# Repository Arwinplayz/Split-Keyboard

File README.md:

# Split-Keyboard
A custom **split keyboard** project built with kicad, fusion 360 and kmk.
---

## Project Overview

This keyboard is a **split design**, fully programmable using KMK firmware. The goal was to design something that would provide a decent typing experience and replace my current keyboard.
---

## Screenshots

### 1. Overall

### 2. Schematic

### 3. PCB layout

### 4. Case Assembly

### Bill Of Materials

| Item | Description | Qty | Unit Price (AUD) | Total Price (AUD) | URL | Running Total (AUD) | USD |
|------|------------|-----|------------------|-------------------|-----|---------------------|-----|
| Kailh Choc Hotswap Socket x10 | Hotswap socket | 1 | $1.52 | $1.52 | [AliExpress](https://www.aliexpress.com/item/1005009439757444.html) | $1.52 | $1.00 |
| Rotary Encoder Module EC11 | Rotary encoder with knob | 2 | $0.43 | $0.86 | [Alibaba](https://www.alibaba.com/product-detail/Yuwah-Factory-Sale-Linear-rotary-Encoder_1601398686693.html) | $2.38 | $1.57 |
| Rotary Encoder Control Button Knob | Rotary encoder knob | 2 | $3.14 | $6.28 | [AliExpress](https://www.aliexpress.com/item/1005002930536102.html) | $8.66 | $5.71 |
| Kailh Low Profile Choc Brown (30 pack) | Switches | 2 | $27.99 | $55.98 | [AliExpress](https://www.aliexpress.com/item/1005005970877769.html) | $58.36 | $38.51 |
| Kailh CHOC Slim Keycaps – Milky White (10 pack) | Keycaps | 2 | $15.69 | $31.38 | [AliExpress](https://www.aliexpress.com/item/1005009153609513.html) | $89.74 | $59.21 |
| 402050 LiPo Battery | Battery | 2 | $3.80 | $7.60 | [AliExpress](https://www.aliexpress.com/item/32662701530.html) | $97.34 | $64.23 |
| JLCPCB Manufacturing | PCB | 1 | $33.00 | $33.00 | [JLCPCB](https://cart.jlcpcb.com/quote) | $130.34 | $86.04 |
| 3D Printed Case | Case | 1 | – | – | – | $130.34 | $86.04 |

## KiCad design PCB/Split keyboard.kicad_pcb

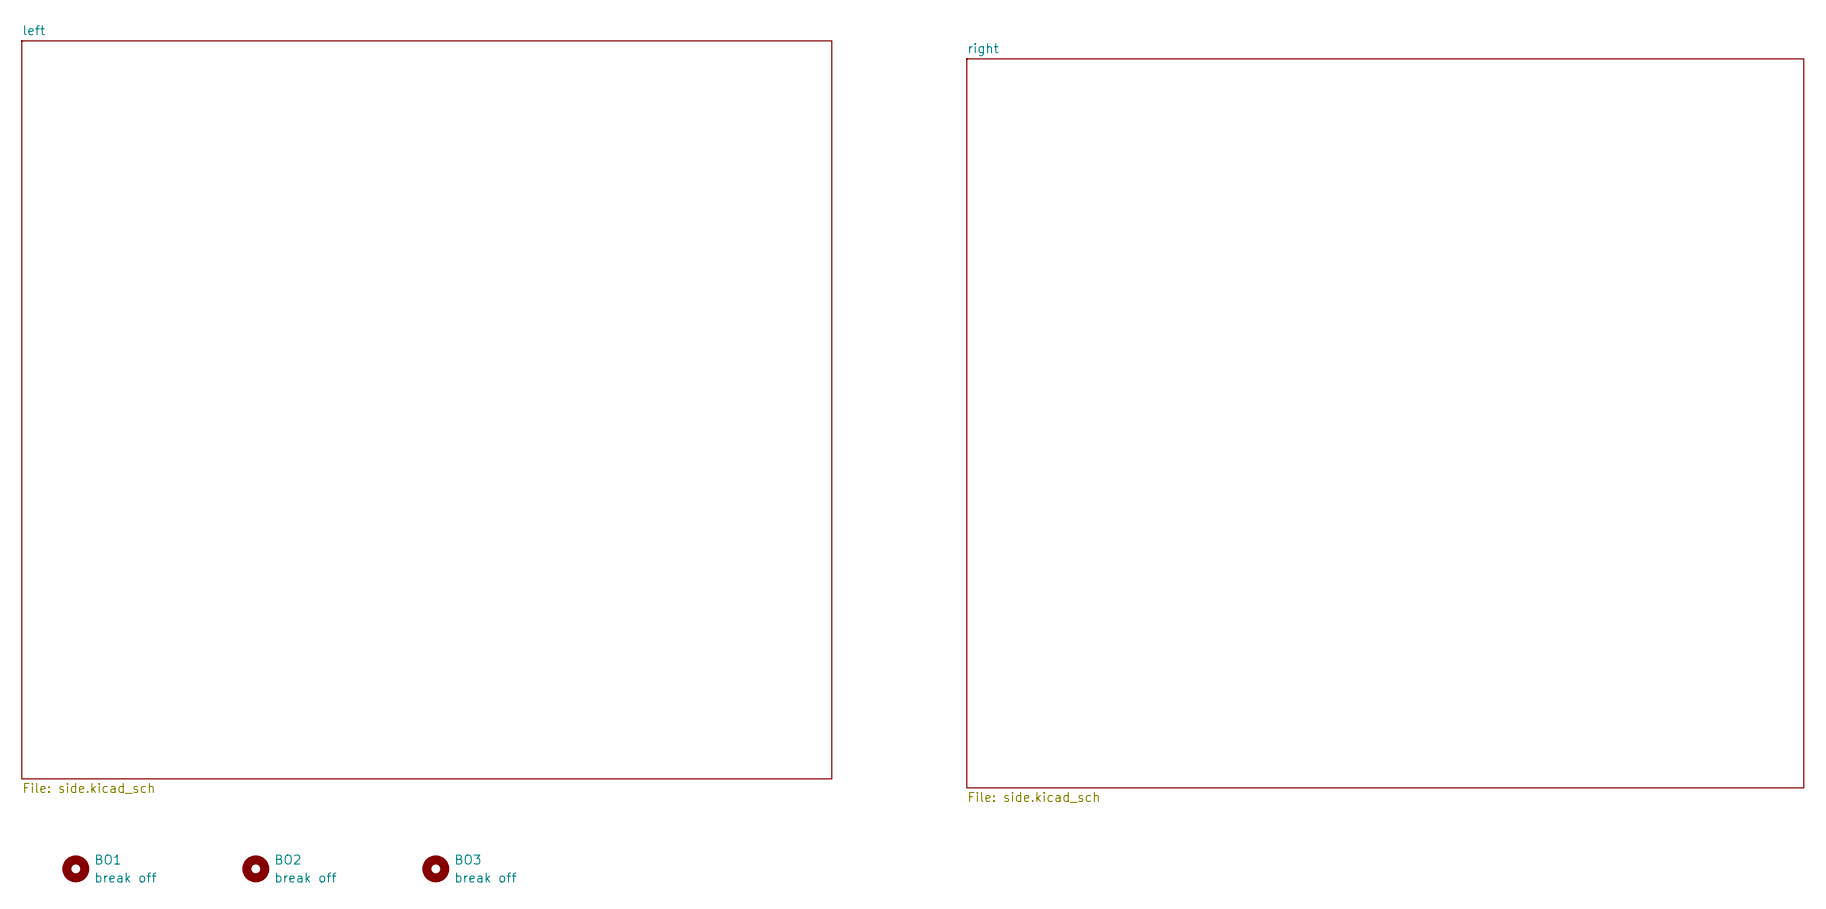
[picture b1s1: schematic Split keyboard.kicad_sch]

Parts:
BO1, BO2, BO3: break off; mouse-bite-5mm-slot

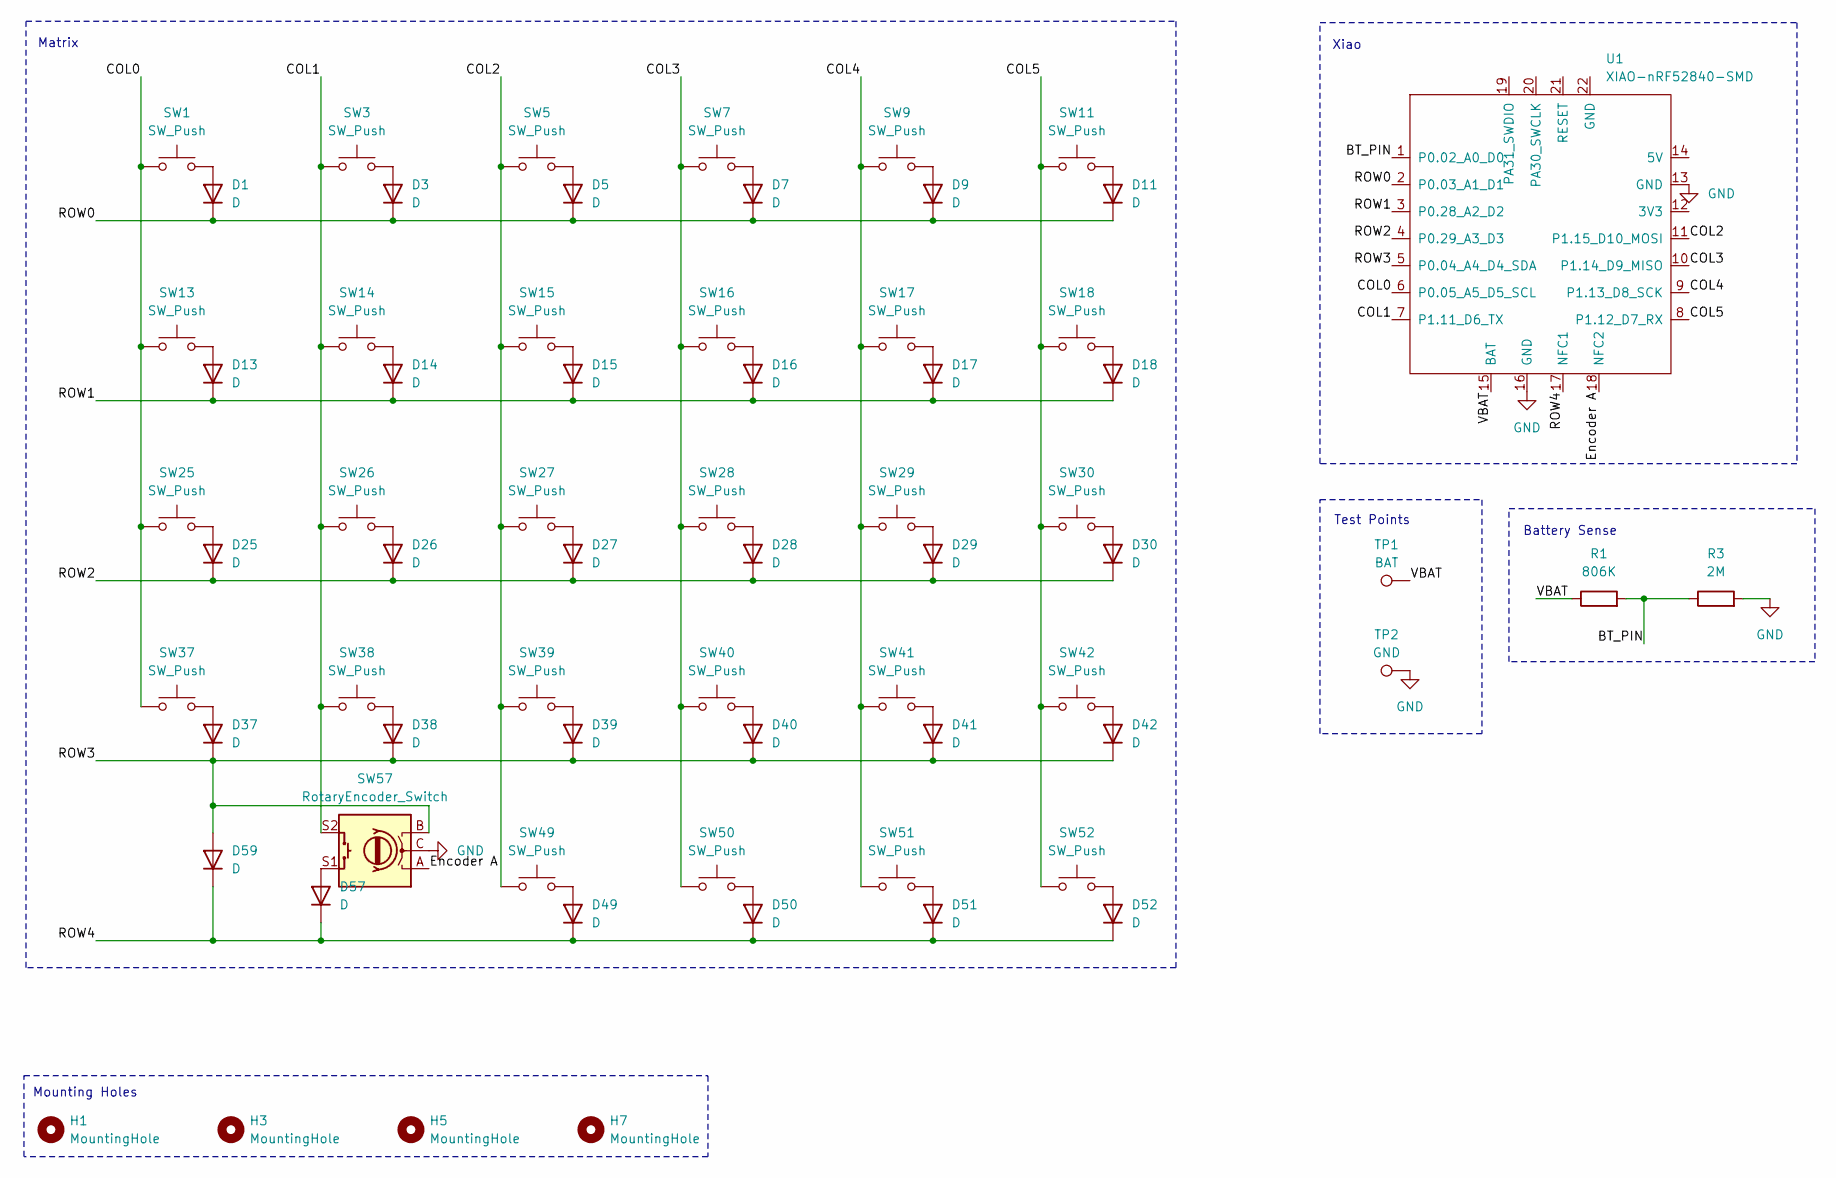
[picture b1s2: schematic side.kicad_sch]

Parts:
D1, D3, D5, D7, D9, D11, D13, D14, D15, D16, D17, D18, D25, D26, D27, D28, D29, D30, D37, D38, D39, D40, D41, D42, D49, D50, D51, D52, D57, D59: D; D_SOD-123
H1, H3, H5, H7: MountingHole; MountingHole_3.2mm_M3
R1: 806K; R_0805_2012Metric
R3: 2M; R_0805_2012Metric
SW1, SW3, SW5, SW7, SW9, SW11, SW13, SW14, SW15, SW16, SW17, SW18, SW25, SW26, SW27, SW28, SW29, SW30, SW37, SW38, SW39, SW40, SW41, SW42, SW49, SW50, SW51, SW52: SW_Push; SW_choc_v1_HS_CPG135001S30_1u
SW57: RotaryEncoder_Switch; RotaryEncoder_Alps_EC11E-Switch_Vertical_H20mm
TP1: BAT; TestPoint_Pad_D2.0mm
TP2: GND; TestPoint_Pad_D2.0mm
U1: XIAO-nRF52840-SMD; modified-XIAO-nRF52840-SMD

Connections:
/left/BT_PIN: R1.2, R3.1, U1.1 (P0.02_A0_D0)
/left/COL0: SW1.1, SW13.1, SW25.1, SW37.1, U1.6 (P0.05_A5_D5_SCL)
/left/COL1: SW3.1, SW14.1, SW26.1, SW38.1, SW57.S2, U1.7 (P1.11_D6_TX)
/left/COL2: SW5.1, SW15.1, SW27.1, SW39.1, SW49.1, U1.11 (P1.15_D10_MOSI)
/left/COL3: SW7.1, SW16.1, SW28.1, SW40.1, SW50.1, U1.10 (P1.14_D9_MISO)
/left/COL4: SW9.1, SW17.1, SW29.1, SW41.1, SW51.1, U1.9 (P1.13_D8_SCK)
/left/COL5: SW11.1, SW18.1, SW30.1, SW42.1, SW52.1, U1.8 (P1.12_D7_RX)
/left/Encoder A: SW57.A, U1.18 (NFC2)
/left/ROW0: D1.1 (K), D3.1 (K), D5.1 (K), D7.1 (K), D9.1 (K), D11.1 (K), U1.2 (P0.03_A1_D1)
/left/ROW1: D13.1 (K), D14.1 (K), D15.1 (K), D16.1 (K), D17.1 (K), D18.1 (K), U1.3 (P0.28_A2_D2)
/left/ROW2: D25.1 (K), D26.1 (K), D27.1 (K), D28.1 (K), D29.1 (K), D30.1 (K), U1.4 (P0.29_A3_D3)
/left/ROW3: D37.1 (K), D38.1 (K), D39.1 (K), D40.1 (K), D41.1 (K), D42.1 (K), D59.2 (A), SW57.B, U1.5 (P0.04_A4_D4_SDA)
/left/ROW4: D49.1 (K), D50.1 (K), D51.1 (K), D52.1 (K), D57.1 (K), D59.1 (K), U1.17 (NFC1)
/left/VBAT: R1.1, TP1.1, U1.15 (BAT)
GND: R3.2, SW57.C, TP2.1, U1.13 (GND), U1.16 (GND); also elsewhere on the board
unnamed: D1.2 (A), SW1.2
unnamed: D3.2 (A), SW3.2
unnamed: D5.2 (A), SW5.2
unnamed: D7.2 (A), SW7.2
unnamed: D9.2 (A), SW9.2
unnamed: D11.2 (A), SW11.2
unnamed: D13.2 (A), SW13.2
unnamed: D14.2 (A), SW14.2
unnamed: D15.2 (A), SW15.2
unnamed: D16.2 (A), SW16.2
unnamed: D17.2 (A), SW17.2
unnamed: D18.2 (A), SW18.2
unnamed: D25.2 (A), SW25.2
unnamed: D26.2 (A), SW26.2
unnamed: D27.2 (A), SW27.2
unnamed: D28.2 (A), SW28.2
unnamed: D29.2 (A), SW29.2
unnamed: D30.2 (A), SW30.2
unnamed: D37.2 (A), SW37.2
unnamed: D38.2 (A), SW38.2
unnamed: D39.2 (A), SW39.2
unnamed: D40.2 (A), SW40.2
unnamed: D41.2 (A), SW41.2
unnamed: D42.2 (A), SW42.2
unnamed: D49.2 (A), SW49.2
unnamed: D50.2 (A), SW50.2
unnamed: D51.2 (A), SW51.2
unnamed: D52.2 (A), SW52.2
unnamed: D57.2 (A), SW57.S1

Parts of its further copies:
D2, D4, D6, D8, D10, D12, D19, D20, D21, D22, D23, D24, D31, D32, D33, D34, D35, D36, D43, D44, D45, D46, D47, D48, D53, D54, D55, D56, D58, D60: D; D_SOD-123
H2, H4, H6, H8: MountingHole; MountingHole_3.2mm_M3
R2: 806K; R_0805_2012Metric
R4: 2M; R_0805_2012Metric
SW2, SW4, SW6, SW8, SW10, SW12, SW19, SW20, SW21, SW22, SW23, SW24, SW31, SW32, SW33, SW34, SW35, SW36, SW43, SW44, SW45, SW46, SW47, SW48, SW53, SW54, SW55, SW56: SW_Push; SW_choc_v1_HS_CPG135001S30_1u
SW58: RotaryEncoder_Switch; RotaryEncoder_Alps_EC11E-Switch_Vertical_H20mm
TP3: BAT; TestPoint_Pad_D2.0mm
TP4: GND; TestPoint_Pad_D2.0mm
U2: XIAO-nRF52840-SMD; modified-XIAO-nRF52840-SMD

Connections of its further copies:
/right/BT_PIN: R2.2, R4.1, U2.1 (P0.02_A0_D0)
/right/COL0: SW2.1, SW19.1, SW31.1, SW43.1, U2.6 (P0.05_A5_D5_SCL)
/right/COL1: SW4.1, SW20.1, SW32.1, SW44.1, SW58.S2, U2.7 (P1.11_D6_TX)
/right/COL2: SW6.1, SW21.1, SW33.1, SW45.1, SW53.1, U2.11 (P1.15_D10_MOSI)
/right/COL3: SW8.1, SW22.1, SW34.1, SW46.1, SW54.1, U2.10 (P1.14_D9_MISO)
/right/COL4: SW10.1, SW23.1, SW35.1, SW47.1, SW55.1, U2.9 (P1.13_D8_SCK)
/right/COL5: SW12.1, SW24.1, SW36.1, SW48.1, SW56.1, U2.8 (P1.12_D7_RX)
/right/Encoder A: SW58.A, U2.18 (NFC2)
/right/ROW0: D2.1 (K), D4.1 (K), D6.1 (K), D8.1 (K), D10.1 (K), D12.1 (K), U2.2 (P0.03_A1_D1)
/right/ROW1: D19.1 (K), D20.1 (K), D21.1 (K), D22.1 (K), D23.1 (K), D24.1 (K), U2.3 (P0.28_A2_D2)
/right/ROW2: D31.1 (K), D32.1 (K), D33.1 (K), D34.1 (K), D35.1 (K), D36.1 (K), U2.4 (P0.29_A3_D3)
/right/ROW3: D43.1 (K), D44.1 (K), D45.1 (K), D46.1 (K), D47.1 (K), D48.1 (K), D60.2 (A), SW58.B, U2.5 (P0.04_A4_D4_SDA)
/right/ROW4: D53.1 (K), D54.1 (K), D55.1 (K), D56.1 (K), D58.1 (K), D60.1 (K), U2.17 (NFC1)
/right/VBAT: R2.1, TP3.1, U2.15 (BAT)
GND: R4.2, SW58.C, TP4.1, U2.13 (GND), U2.16 (GND); also elsewhere on the board
unnamed: D2.2 (A), SW2.2
unnamed: D4.2 (A), SW4.2
unnamed: D6.2 (A), SW6.2
unnamed: D8.2 (A), SW8.2
unnamed: D10.2 (A), SW10.2
unnamed: D12.2 (A), SW12.2
unnamed: D19.2 (A), SW19.2
unnamed: D20.2 (A), SW20.2
unnamed: D21.2 (A), SW21.2
unnamed: D22.2 (A), SW22.2
unnamed: D23.2 (A), SW23.2
unnamed: D24.2 (A), SW24.2
unnamed: D31.2 (A), SW31.2
unnamed: D32.2 (A), SW32.2
unnamed: D33.2 (A), SW33.2
unnamed: D34.2 (A), SW34.2
unnamed: D35.2 (A), SW35.2
unnamed: D36.2 (A), SW36.2
unnamed: D43.2 (A), SW43.2
unnamed: D44.2 (A), SW44.2
unnamed: D45.2 (A), SW45.2
unnamed: D46.2 (A), SW46.2
unnamed: D47.2 (A), SW47.2
unnamed: D48.2 (A), SW48.2
unnamed: D53.2 (A), SW53.2
unnamed: D54.2 (A), SW54.2
unnamed: D55.2 (A), SW55.2
unnamed: D56.2 (A), SW56.2
unnamed: D58.2 (A), SW58.S1

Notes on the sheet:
Xiao
Battery Sense
Mounting Holes
Matrix
Test Points

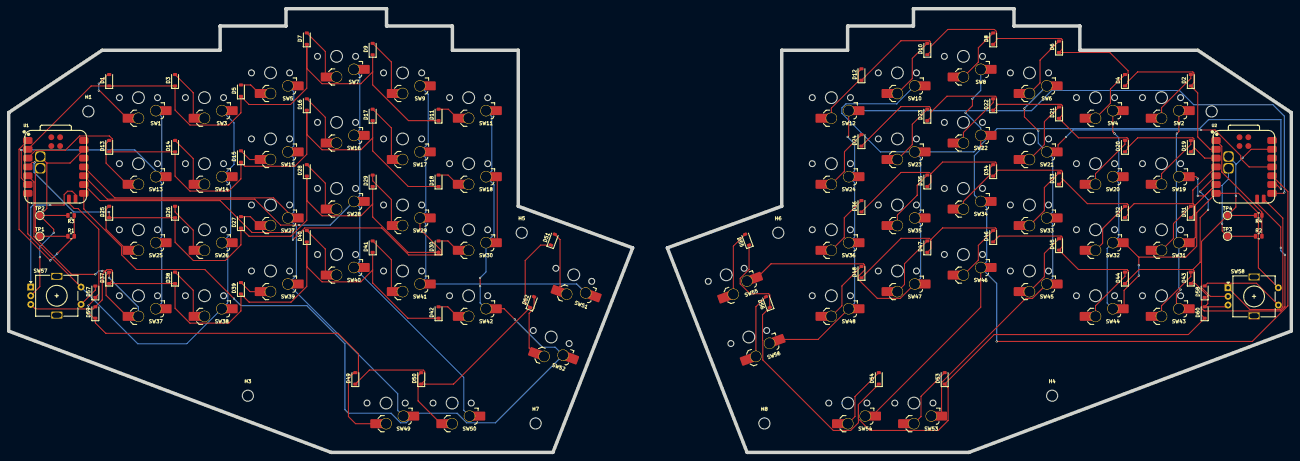
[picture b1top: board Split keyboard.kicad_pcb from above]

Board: 2 copper layers, 370.0 x 128.0 mm, 136 parts (1 on the bottom side), 87 nets.

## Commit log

2025-12-17 Add local project files
2025-12-17 Enhance README with project details and images
    Expanded project description and added screenshots.
2025-12-17 Added BOM
2025-12-17 Add Bill of Materials section to README
    Added a Bill of Materials (BOM) section with item details, quantities, prices, and URLs.
2025-12-17 Update Bill of Materials with new pricing and items
2025-12-17 Revise Bill of Materials with updated items and prices
    Updated the Bill of Materials (BOM) section with new items and pricing, including USD conversions.
2025-12-18 Revise quantities and prices in BOM for keyboard
    Updated quantities and prices for various components in the Bill of Materials.
2025-12-18 Update Bill Of Materials with new item details
2026-03-23 added blog
